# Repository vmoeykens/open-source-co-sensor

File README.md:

# Open Source CO Sensor
## Hardware
All hardware design is done in KiCad and is stored in a KiCad .pro file in the hardware folder. All hardware changes are versioned controlled. Schematics are found in PDF form in the hardware folder.  
## Software

## 3D CAD Models

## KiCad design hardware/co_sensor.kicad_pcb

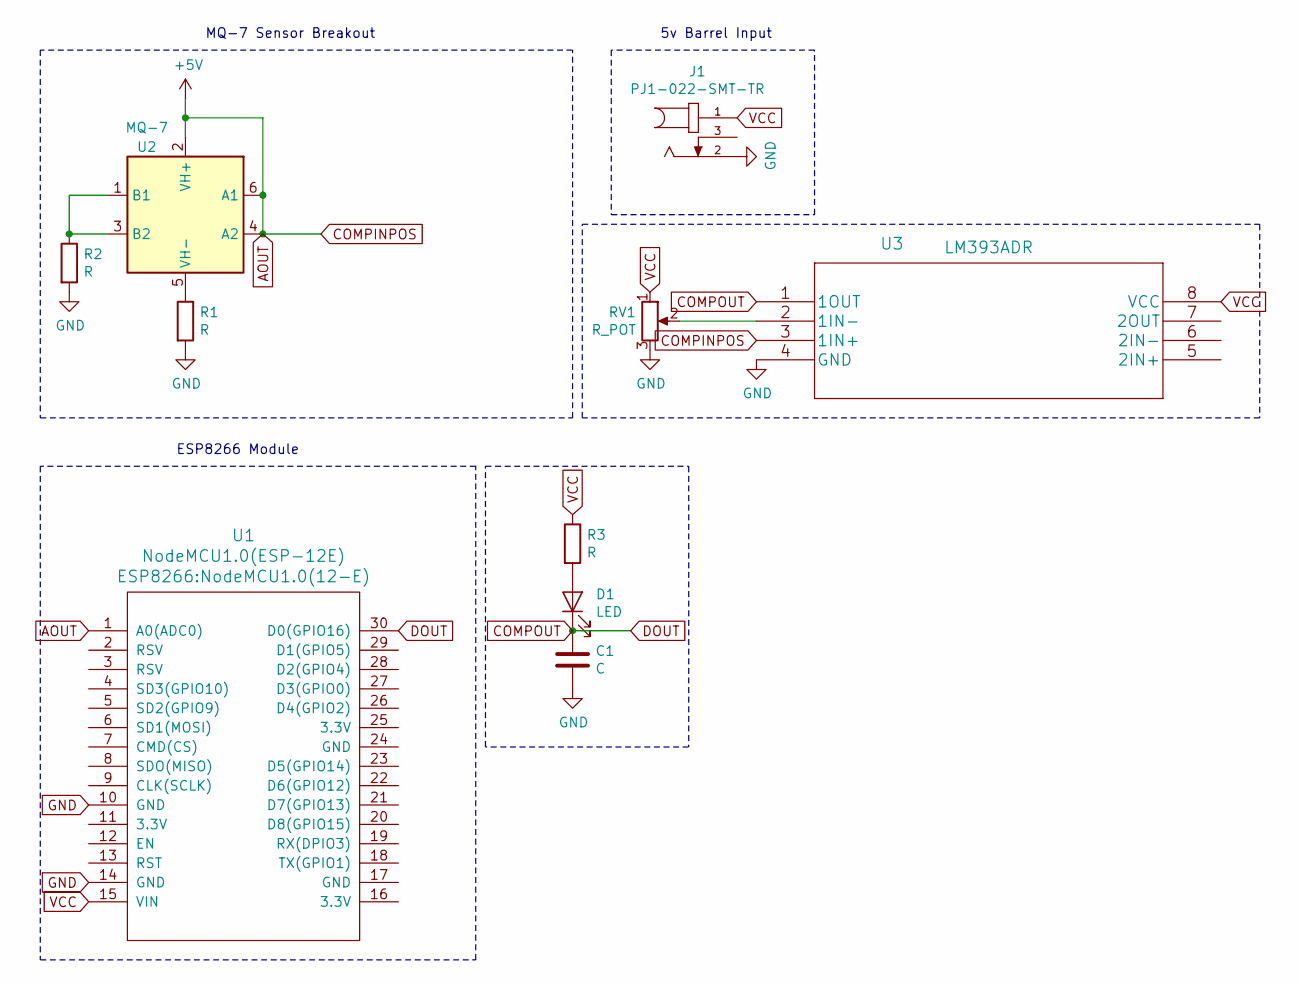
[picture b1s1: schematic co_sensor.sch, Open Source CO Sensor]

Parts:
C1: C; C_0805_2012Metric
D1: LED; D_1206_3216Metric
J1: PJ1-022-SMT-TR; CUI_PJ1-022-SMT-TR
R1, R2, R3: R; R_0805_2012Metric
RV1: R_POT; Potentiometer_ACP_CA9-VSMD_Vertical
U1: NodeMCU1.0(ESP-12E); NodeMCU1.0(12-E)
U2: MQ-7; MQ-6
U3: LM393ADR

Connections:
AOUT: U1.1 (A0(ADC0)), U2.2 (VH+), U2.4 (A2), U2.6 (A1), U3.3 (1IN+)
COMPOUT: C1.1, D1.1 (K), U1.30 (D0(GPIO16)), U3.1 (1OUT)
GND: C1.2, J1.2, R1.2, R2.2, RV1.3, U1.10 (GND), U1.14 (GND), U3.4 (GND)
unnamed: D1.2 (A), R3.2
unnamed: R1.1, U2.5 (VH-)
unnamed: R2.1, U2.1 (B1), U2.3 (B2)
unnamed: RV1.2, U3.2 (1IN-)
VCC: J1.1, R3.1, RV1.1, U1.15 (VIN), U3.8 (VCC)

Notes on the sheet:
MQ-7 Sensor Breakout
5v Barrel Input
ESP8266 Module

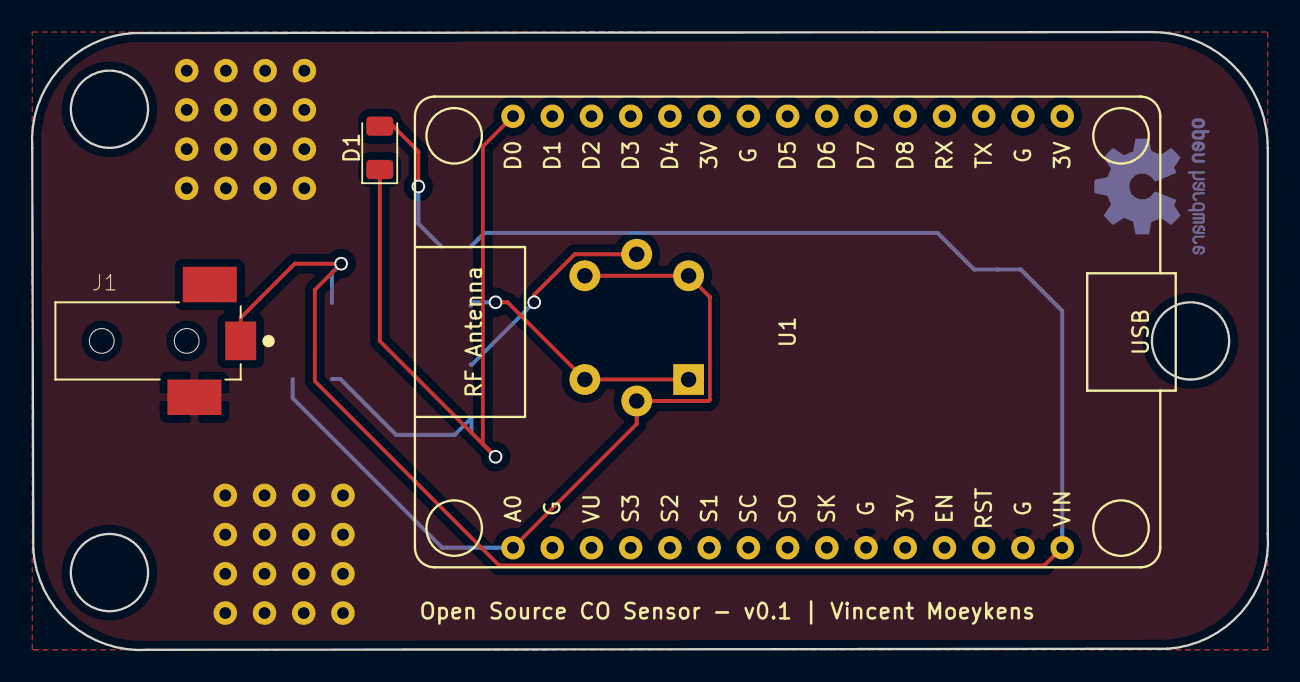
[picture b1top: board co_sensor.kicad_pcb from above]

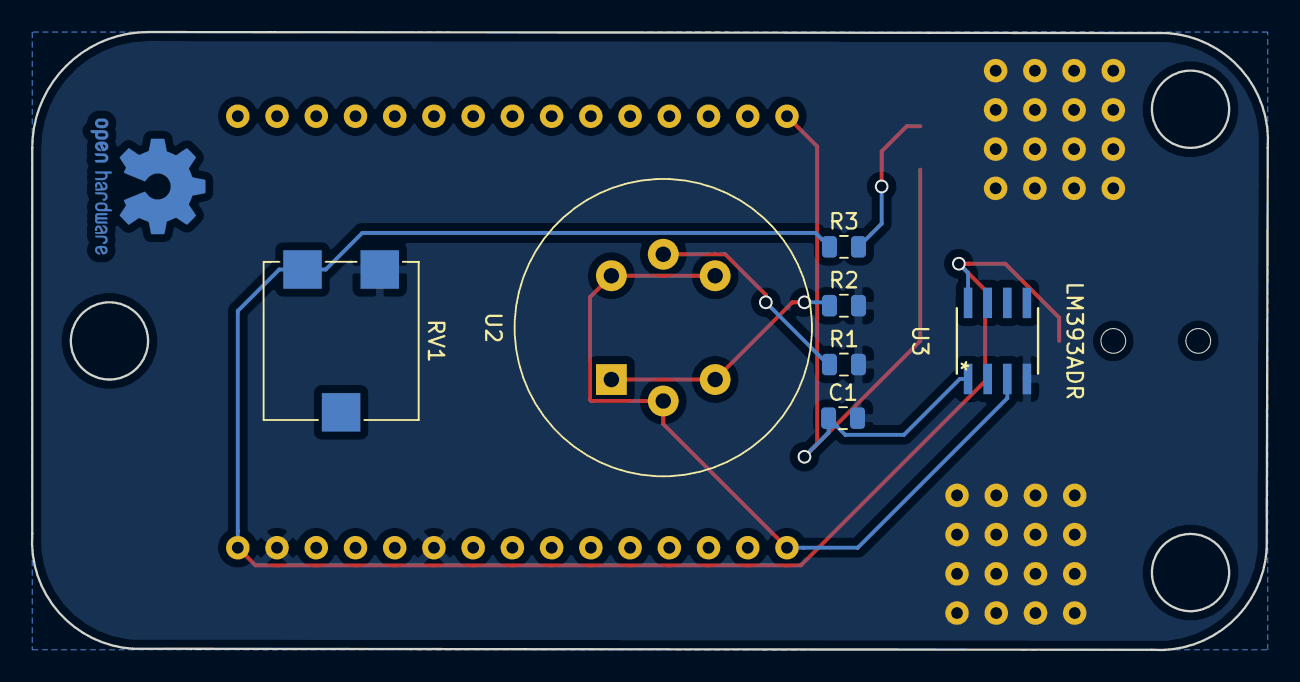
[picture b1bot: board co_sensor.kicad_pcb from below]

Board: 2 copper layers, 80.0 x 40.0 mm, 10 parts (7 on the bottom side), 8 nets.

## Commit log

2019-12-03 Adds new readme
2020-01-17 Updates README.md
2020-01-17 Adds PDF schematic file
2020-01-17 Updates schematic file and adds an empty gitignore
2020-05-05 Completely refactors the board with a new sensor and processor. Adds a .gitignore
2020-05-06 Updates with new LM393AR footprint and schematic item
2020-05-06 Updates PDF of schematic
2020-05-06 Adds gerber file and updates schematic to include hardware in BOM

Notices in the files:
parts and their libraries:
Copyright 2016 Accelerated Designs. All rights reserved.
